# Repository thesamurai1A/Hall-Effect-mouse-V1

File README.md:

# Hall-Effect-mouse-V1
This is a mouse with hall effect switches that I made after 1 week of starting electrical engineering( since I'm in high school math and some things might be flawed but I will update the designs)

Wiring and components is as follow:
U1/stm32f042k6ux

PB0: SDA
PB1: SCL
VDD: VBUS and Ground through C1
VSS: Ground 
PA0: Vout U2
PA1: Vout U3
PA2: SW1 through R2 
PA3: SW2
PA4: SW3
PA5: SW4
PA6: SCLK
PA7: M0SI
PA8: TxD0
PA9: RxD0
PA11: D-
PA12: D+ through R1
PA13: MISO
PA14: CS
PA15: IRQ

U2/drv5053vaqdbzr

VCC: Vbus
GND: Ground
Vout: PA1

U3/drv5053vaqdbzr

VCC: Vbus
GND: Ground
Vout: PA0

U4/PMW3360dm-t2qu

VDD: Vbus
GND: Ground 
LED_P: Vbus
Reset: SW1 through R3
SCLK: PA6
MOSI: PA7
MISO: PA13
CS: PA14
P1/USB_C_Plug_USB2.0

Vbus: CC, Ground and other components power connections 
CC: Vbus
D-: PA11
D+: PA12 through R
GND: Vbus and Ground
Shield: Ground through C3

MOD1/ESP32-WROOM-32

3v3: Vbus
TxDO: PA8
RxDO: PA9
GND: ground 
GND: ground 
GND: ground 
GND: ground 

U5/MPR121QR2

VDD: Vbus
VSS: Ground parallel C2
SDA: PB0
SCL: PB1
IRQ: PA15

SW1

PIN1: PA2 through R2 and reset U4
PIN2: Ground

SW2

PIN1: PA3
PIN2: Ground

SW3

PIN1: PA4
PIN2: Ground

SW4

PIN1: PA5
PIN2: Ground

C1: VDD and VDD to ground 

C2: Parallel to VSS and ground 

C3: Shield and ground

C4: Vbus and GND

C5: Parallel to U4GND and ground 

R1: PA12 and D+

R2: PA2 and SW1

R3: Parallel to R2 connected to SW1 wiring 

R4: Connected in parallel Vbus and LED_P

R5: Connected in parallel to VDD and Vbus

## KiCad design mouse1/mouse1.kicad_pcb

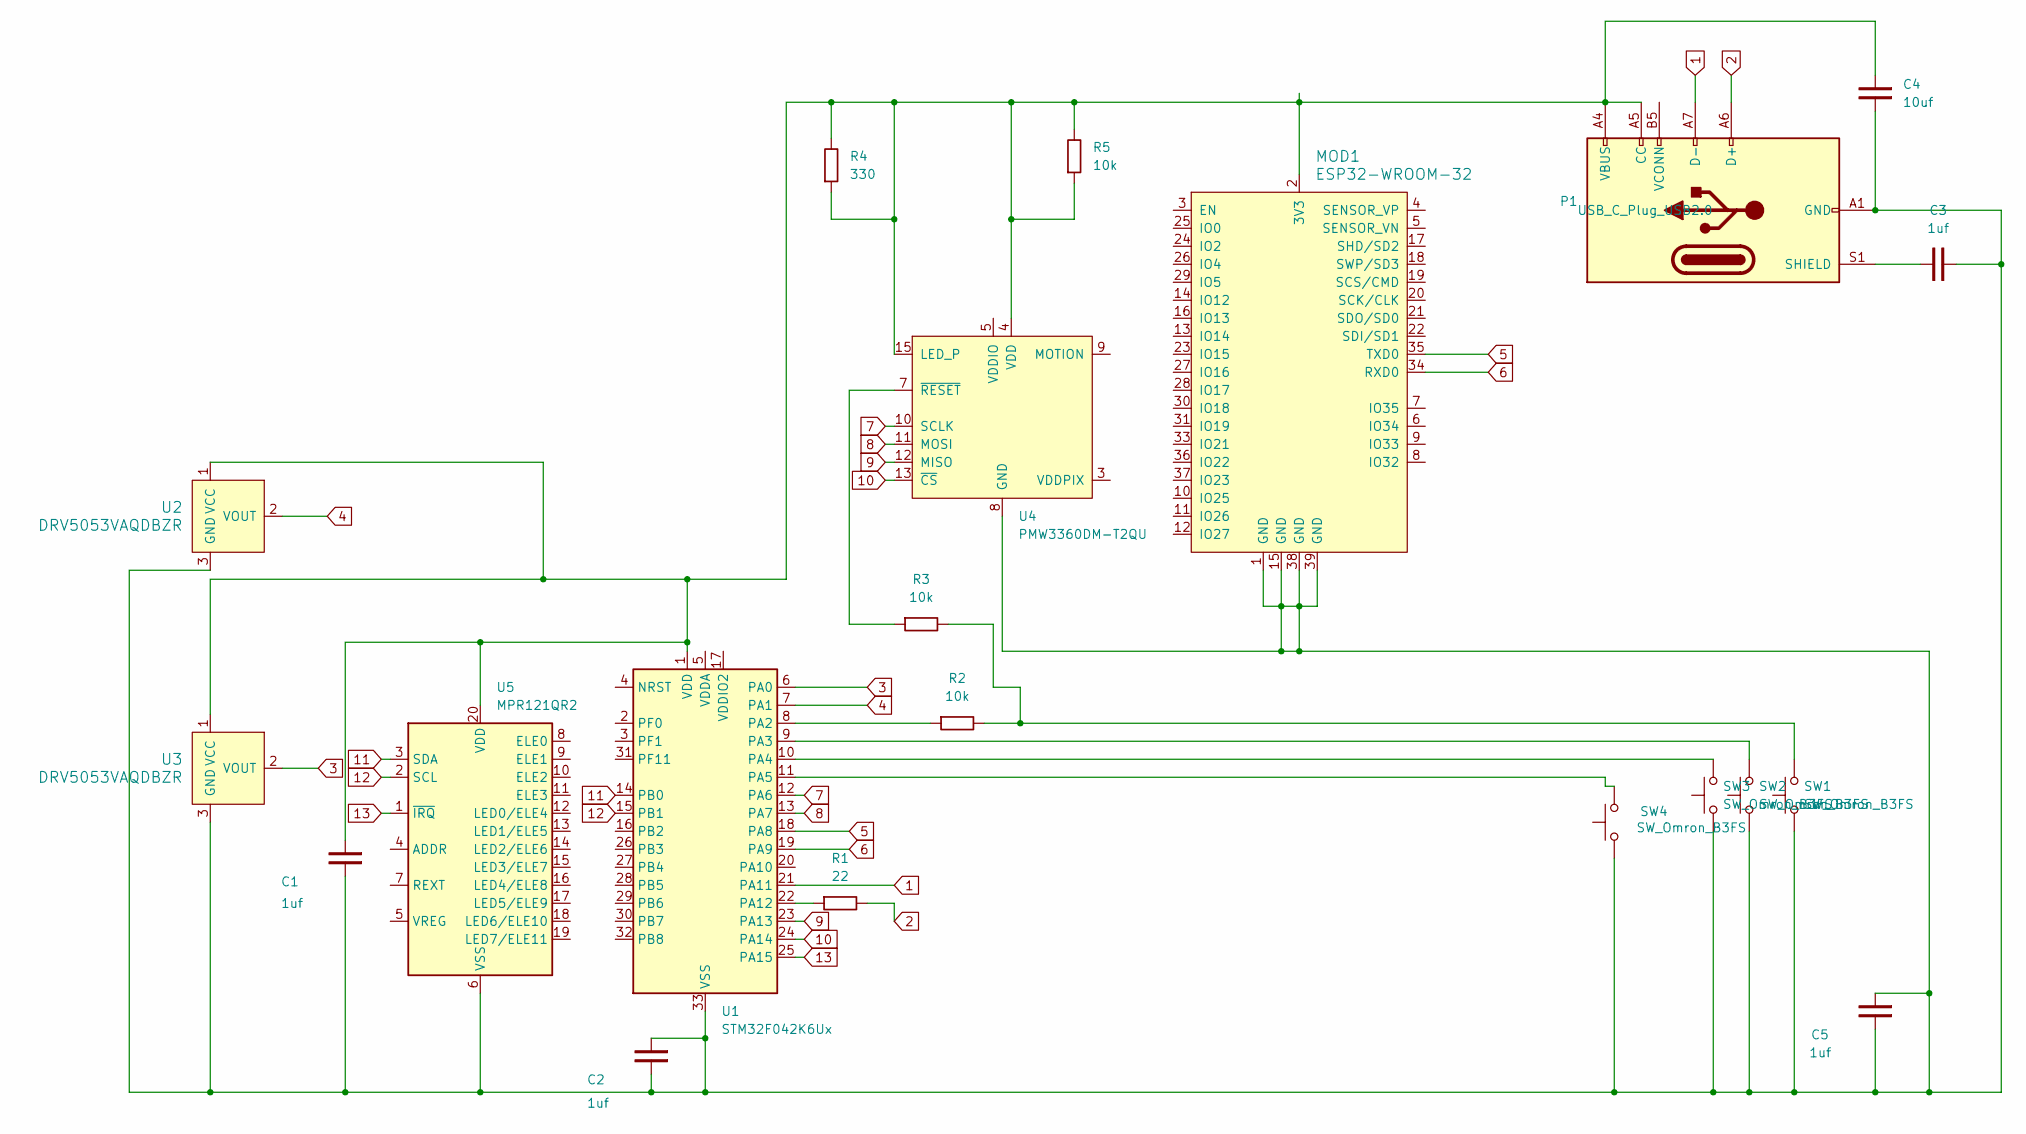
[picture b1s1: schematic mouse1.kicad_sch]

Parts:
C1, C2, C3, C5: 1uf; C_0805_2012Metric_Pad1.18x1.45mm_HandSolder
C4: 10uf; C_0805_2012Metric_Pad1.18x1.45mm_HandSolder
MOD1: ESP32-WROOM-32; ESP32-WROOM-32D; MPN ESP32-WROOM-32; Digi-Key_PN 1904-1010-1-ND
P1: USB_C_Plug_USB2.0; USB_C_Receptacle_XKB_U262-16XN-4BVC11
R1: 22; R_0805_2012Metric
R2, R3, R5: 10k; R_0805_2012Metric
R4: 330; R_0805_2012Metric
SW1: SW_Omron_B3FS; SW_SPST_Omron_B3FS-100xP
SW2, SW3: SW_Omron_B3FS; SW_Alps_Matias
SW4: SW_Omron_B3FS; SW_Push_1P1T_NO_CK_PTS125Sx43PSMTR
U1: STM32F042K6Ux; QFN-32-1EP_5x5mm_P0.5mm_EP3.45x3.45mm
U2, U3: DRV5053VAQDBZR; SOT-23-3; MPN DRV5053VAQDBZR; Digi-Key_PN 296-38460-1-ND
U4: PMW3360DM-T2QU; PMW3360
U5: MPR121QR2; UQFN-20_3x3mm_P0.4mm

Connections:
1: P1.A7 (D-), U1.21 (PA11)
2: P1.A6 (D+), R1.2
3: U1.6 (PA0), U3.2 (VOUT)
4: U1.7 (PA1), U2.2 (VOUT)
5: MOD1.35 (TXD0), U1.18 (PA8)
6: MOD1.34 (RXD0), U1.19 (PA9)
7: U1.12 (PA6), U4.10 (SCLK)
8: U1.13 (PA7), U4.11 (MOSI)
9: U1.23 (PA13), U4.12 (MISO)
10: U1.24 (PA14), U4.13 (~CS)
11: U1.14 (PB0), U5.3 (SDA)
12: U1.15 (PB1), U5.2 (SCL)
13: U1.25 (PA15), U5.1 (~IRQ)
unnamed: C1.1, C4.1, MOD1.2 (3V3), P1.A4 (VBUS), P1.A5 (CC), P1.A9 (VBUS), P1.B4 (VBUS), P1.B9 (VBUS), R4.1, R4.2, R5.1, R5.2, U1.1 (VDD), U2.1 (VCC), U3.1 (VCC), U4.4 (VDD), U4.15 (LED_P), U5.20 (VDD)
unnamed: C3.2, P1.S1 (SHIELD)
unnamed: R2.2, R3.2, SW1.2
unnamed: R2.1, U1.8 (PA2)
unnamed: SW2.2, U1.9 (PA3)
unnamed: SW3.2, U1.10 (PA4)
unnamed: SW4.2, U1.11 (PA5)
unnamed: R1.1, U1.22 (PA12)
unnamed: C1.2, C2.1, C2.2, C3.1, C4.2, C5.1, C5.2, MOD1.1 (GND), MOD1.15 (GND), MOD1.38 (GND), MOD1.39 (GND), P1.A1 (GND), P1.A12 (GND), P1.B1 (GND), P1.B12 (GND), SW1.1, SW2.1, SW3.1, SW4.1, U1.33 (VSS), U2.3 (GND), U3.3 (GND), U4.8 (GND), U5.6 (VSS)
unnamed: R3.1, U4.7 (~RESET)

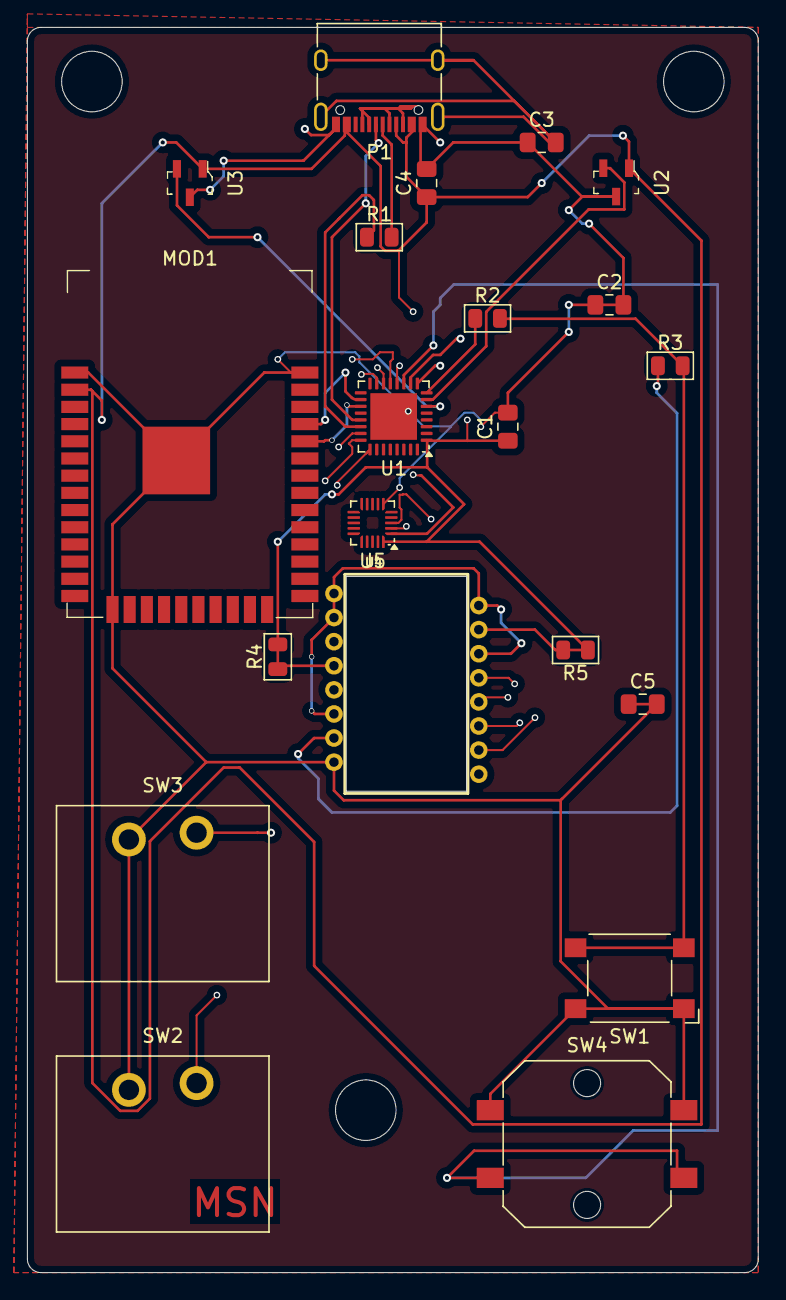
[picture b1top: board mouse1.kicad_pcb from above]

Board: 4 copper layers, 54.0 x 92.0 mm, 21 parts (0 on the bottom side), 23 nets.
